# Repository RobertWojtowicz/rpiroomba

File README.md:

# RPiRoomba

## 1. Introduction
This project is based on the following projects:
- https://github.com/pomeroyb/Create2Control
- https://github.com/silvanmelchior/RPi_Cam_Web_Interface

## 2. How does this work?
- the project applies only to Roomba models that have 7-pin Mini-DIN serial port (iRobot Create Intereface);
- please note that different Roomba models have in different places this port, the PCB was designed for the Roomba 620;
- in case of Roomba 620 you have to cut a hole in the bezel to get to Mini-DIN serial port (the bezel is replaceable, in different colors ;-) to remove the bezel follow the instructions in this project: https://github.com/joric/joirc;
- the port was connected through a logical level converter together with Raspberry Pi Zero W;
- Raspberry Pi Zero W was connected to the camera, LED driver and micro servo, as in the images below:

- the project allows you to remotely control Roomba (via WiFi), watch live video and record, take pictures;
- it is possible to run a cleaning schedule, which Roomba 620 does not have;
- infrared high power LED chip allows visibility of the camera at night;
- it is possible to adjust the camera position angle (0°, 30°, 60°, 90°).

## 3. Build hardware
- create your own PCB v1.1 according to the project files: roomba_led_pcb_v1.sch, roomba_led_pcb_v1.brd, roomba_main_pcb_v1.sh, roomba_main_pcb_v1.brd from this repository (files location: rpiroomba/pcb/), example of finished PCBs v1.0 below:

- prepare the aluminium housing - heat sink for CPU Raspberry Pi Zero W and high power LED chip, similar to the picture (dimensions approx: 36 mm x 65 mm):
- add a thermal pad under the high power LED chip and the CPU Raspberry Pi Zero W to dissipate the heat to the aluminium case;

- the hinges come from the elements of the electric cube;
- metric screws with a diameter of 2 mm were used to connect the parts;
- reduce the current on the LED driver from 700 mA to 230 mA (too high power causes unreadable view);
- set a voltage of 5V on the step-down DC/DC module;
- isolate the Raspberry Pi and camera pins from accidental short circuits, as shown in the following picture:

- isolate the IR sensor on the Roomba in half with tape, as shown in the following picture (otherwise the docking station search algorithm will fail when the Raspberry Pi Zero W module is installed):

The following parts are required:
- Modules: 1x DC/DC step-down MP1584EN, 1x Raspberry Pi Zero W V1.1, 1x Raspberry Pi NoIR Camera V2, 1x LED driver PT4115:<br>

- 1x Camera adaptor (cable) from official case Raspberry Pi Zero;
- 1x Micro servo TowerPro MG90S;
- 1x SMD 1206 high power LED chip, 3W IR 850 Nm;
- 1x SMD 1206 resettable polymeric fuse 500 mA;
- 1x SMD 1206 resistors: 15 Ohm, 120 Ohm, 390 Ohm, 1 kOhm;
- 3x SMD 1206 zener diode 3.3 V;
- 1x 40 pin, 2.54 mm, single in line, 20 mm long, header male;
- 1x 40 pin, 2.54 mm, single in line, right angle, header male.

## 4. Preparing Linux system (tested on current kernel 5.15.56+)
- download Raspberry Pi OS (32-bit) Lite system image: https://downloads.raspberrypi.org/raspios_lite_armhf_latest;
- upload system to the microSD card, using Raspberry PI Imager, all you need is a 4 GB microSD card with UHS-1 speed class;
- in Raspberry PI Imager advanced options, set: Enable SSH, Set username and password, Configure wireless LAN;
- on the boot partition replace or edit "config.txt" file based on an example from this repository (file location: /rpi/boot/);
- to disable HDMI (to reduce the power consumption) you must replace or edit "rc.local" file based on an example from this repository (file location: rpiroomba/rpi/etc/);
- install modules: sudo apt-get install python3-pip, sudo pip install pyserial.

## 5. Installing RPi-CAM-Web-Interface (tested on current version 6.6.26)
To install RPi-CAM-Web-Interface, run the following commands:
- sudo apt-get install git;
- git clone https://github.com/silvanmelchior/RPi_Cam_Web_Interface.git;
- cd RPi_Cam_Web_Interface;
- ./install.sh;
- in the configuration menu, clear the "xCam subfolder" option, add the user in "xUser:" admin and the password "xPassword:" and select OK;
- when the installation is complete you can delete folder, rm -rf RPi_Cam_Web_Interface;
- change the autostart parameter to idle in /etc/raspimjpeg (to disable the automatic start of the camera when starting Raspberry Pi);
- change the parameters in the browser under Camera Settings to: Load Preset: HD-ready 720p, Rotation: Rotate_270, Preview quality: Quality: 10, Width 1280, Divider: 1, for example picture of RPI Cam interface:

## 6. Configuring scripts
- create a roomba folder in /var/www/ directory and then copy the files, e.g. using WinSCP from this repository (file location: /rpi/www/roomba/): command.php, config.json, create2api.py, jquery-3.6.0.min.js, roomba.py, submit.js;
- in /var/www/ directory, you should replace index.html from this repository (file location: /rpi/www/);
- grant permissions for user-data: sudo usermod -a -G gpio www-data, sudo usermod -a -G gpio $USER, sudo usermod -a -G dialout www-data;
- grant permissions to execute files, chmod +x /var/www/roomba/*

## 7. Creating a cleaning schedule
- Roomba 620 does not have its own cleaning schedule, but you can add in cron;
- for example, Monday, Wednesday, Friday at 12:00 you should edit the file using the command crontab -e:<br/> 
00 12 * * 1 python3 /var/www/roomba/roomba.py clean<br/>
00 12 * * 3 python3 /var/www/roomba/roomba.py clean<br/>
00 12 * * 5 python3 /var/www/roomba/roomba.py clean

## 8. Some final project photos
- Camera down (position angle 0°):

- Current limit adjustment on LED driver:

- Camera up (position angle 90°):

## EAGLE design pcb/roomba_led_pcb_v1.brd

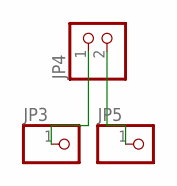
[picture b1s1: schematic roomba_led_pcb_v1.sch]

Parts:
JP3, JP5: PINHD-1X1; 1X01
JP4: PINHD-1X2/90; 1X02/90

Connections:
unnamed: JP3.1, JP4.1
unnamed: JP4.2, JP5.1

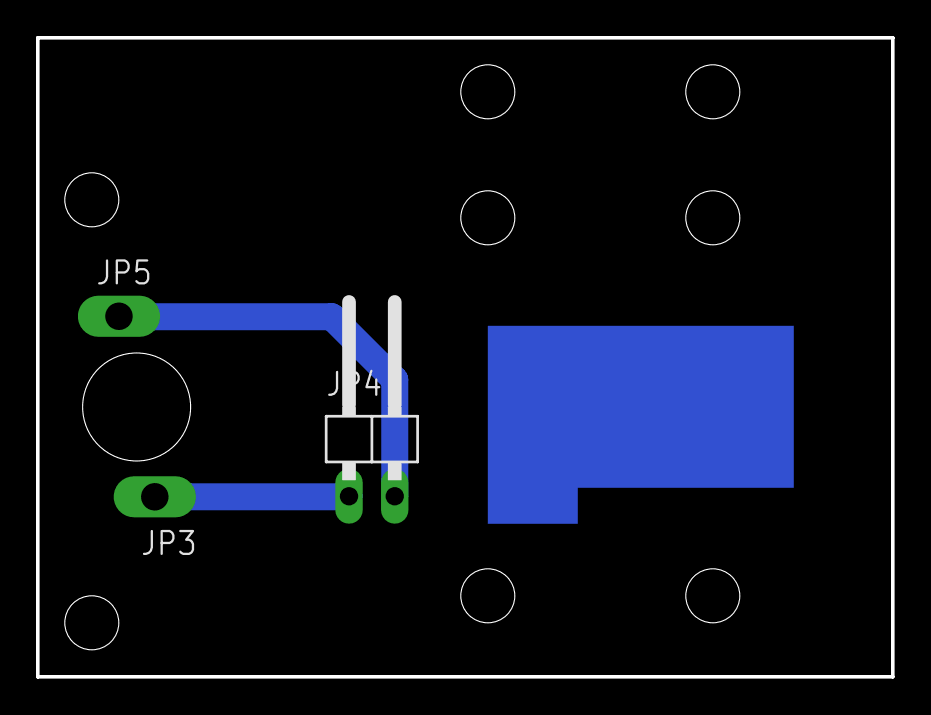
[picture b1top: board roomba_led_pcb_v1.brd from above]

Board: 2 copper layers, 47.5 x 35.5 mm, 3 parts (0 on the bottom side), 2 nets.

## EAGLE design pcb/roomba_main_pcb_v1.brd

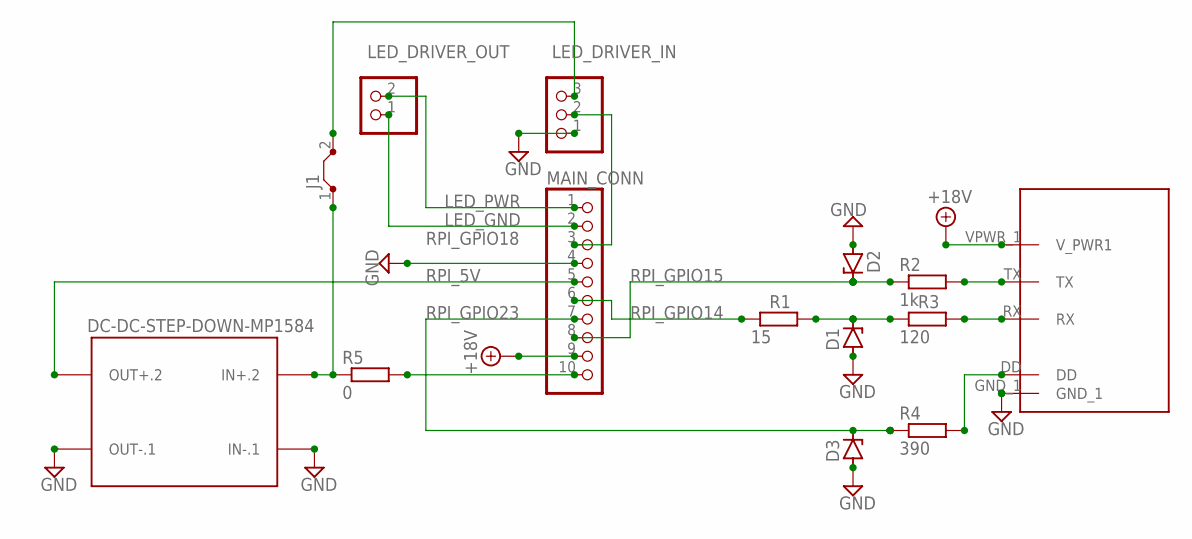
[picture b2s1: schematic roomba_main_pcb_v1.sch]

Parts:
D1, D2, D3: ZENER-DIODESOD80C; SOD80C
J1: J25MM; 25
LED_DRIVER_IN: PINHD-1X3; 1X03
LED_DRIVER_OUT: PINHD-1X2; 1X02
MAIN_CONN: PINHD-1X10/90; 1X10/90
R1: 15; M1206
R2: 1k; M1206
R3: 120; M1206
R4: 390; M1206
R5: 0; M1206
ROOMBA_PORT: 7_PIN; PIN-7
U$1: DC-DC-STEP-DOWN-MP1584

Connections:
+18V: MAIN_CONN.9, ROOMBA_PORT.VPWR_1 (V_PWR1)
GND: D1.A, D2.A, D3.A, LED_DRIVER_IN.1, MAIN_CONN.4, ROOMBA_PORT.GND_1, U$1.IN-.1, U$1.OUT-.1
LED_GND: LED_DRIVER_OUT.1, MAIN_CONN.2
LED_PWR: LED_DRIVER_OUT.2, MAIN_CONN.1
unnamed: J1.1, R5.1, U$1.IN+.2
unnamed: R4.2, ROOMBA_PORT.DD
unnamed: J1.2, LED_DRIVER_IN.3
unnamed: R3.2, ROOMBA_PORT.RX
unnamed: D1.C, R1.2, R3.1
unnamed: R2.2, ROOMBA_PORT.TX
unnamed: MAIN_CONN.10, R5.2
RPI_5V: MAIN_CONN.5, U$1.OUT+.2
RPI_GPIO14: MAIN_CONN.6, R1.1
RPI_GPIO15: D2.C, MAIN_CONN.8, R2.1
RPI_GPIO18: LED_DRIVER_IN.2, MAIN_CONN.3
RPI_GPIO23: D3.C, MAIN_CONN.7, R4.1

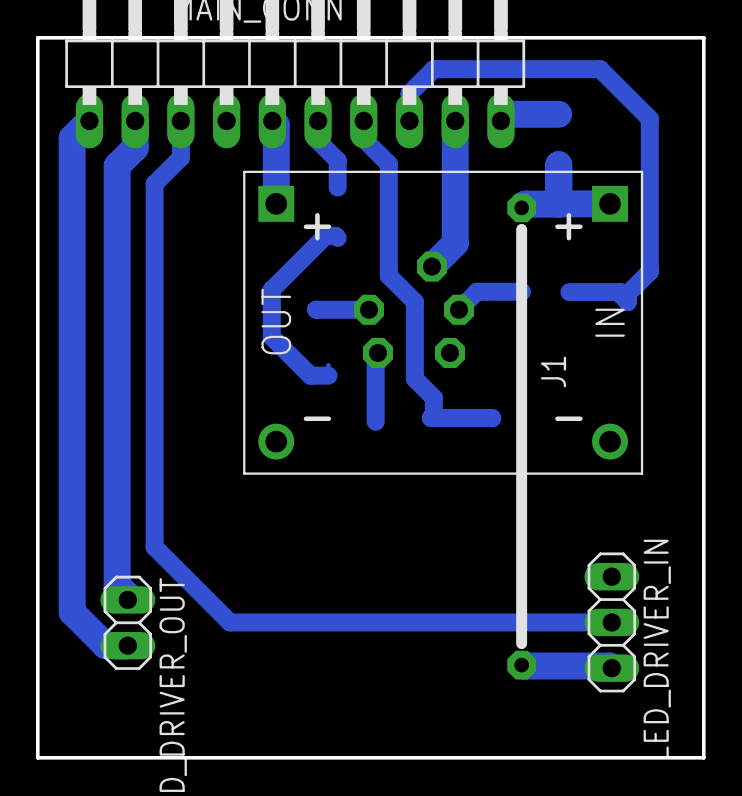
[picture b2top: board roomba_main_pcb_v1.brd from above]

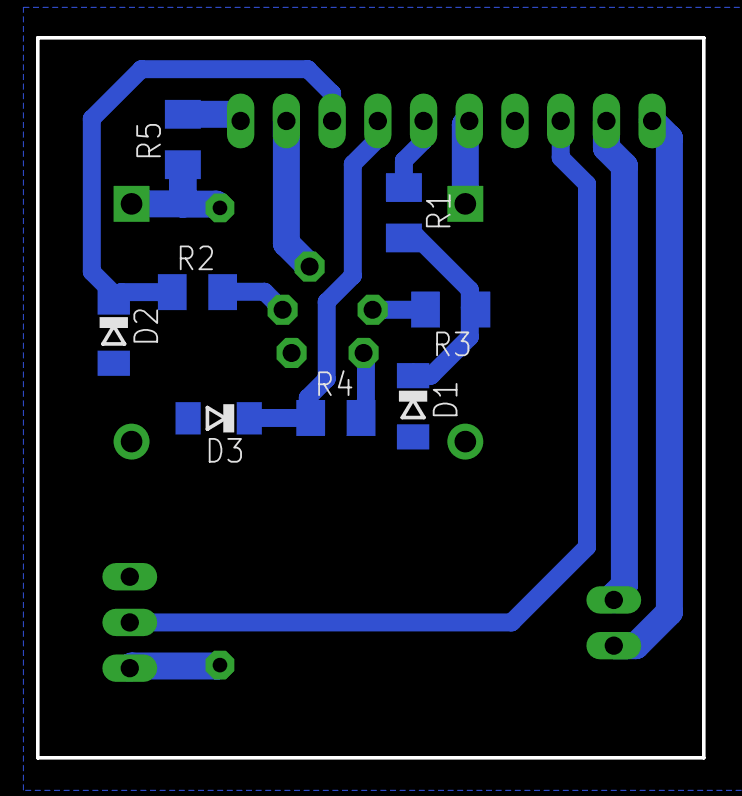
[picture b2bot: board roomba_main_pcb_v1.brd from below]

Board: 2 copper layers, 37.0 x 40.0 mm, 14 parts (8 on the bottom side), 16 nets.

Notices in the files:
parts and their libraries:
diy-modules: Released under the Creative Commons Attribution 4.0 International License: http://creativecommons.org/licenses/by/4.0
